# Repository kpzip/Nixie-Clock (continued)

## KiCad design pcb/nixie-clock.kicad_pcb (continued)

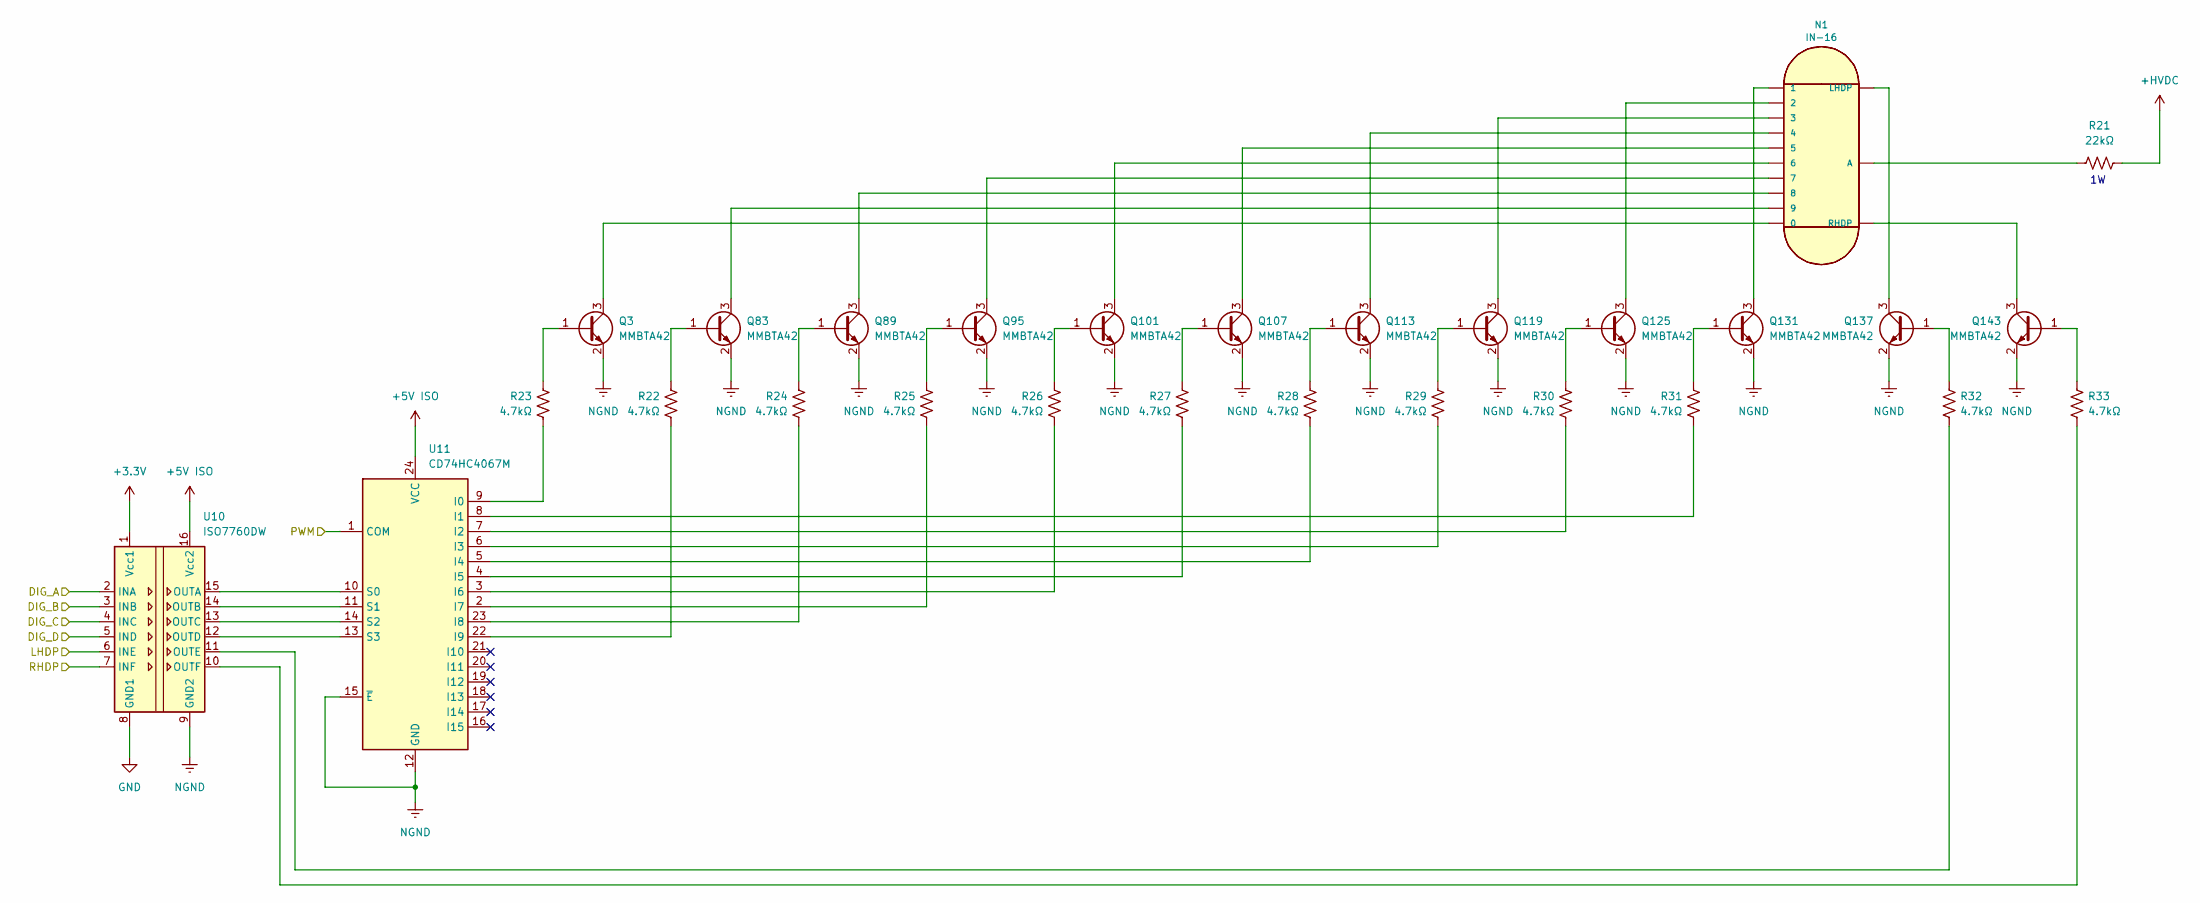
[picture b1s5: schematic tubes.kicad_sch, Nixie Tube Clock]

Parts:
N1: IN-16; nixies-us-IN-16
Q3, Q83, Q89, Q95, Q101, Q107, Q113, Q119, Q125, Q131, Q137, Q143: MMBTA42; SOT-23
R21: 22kΩ; R_2512_6332Metric
R22, R23, R24, R25, R26, R27, R28, R29, R30, R31, R32, R33: 4.7kΩ; R_0603_1608Metric
U10: ISO7760DW; SOIC-16W_7.5x10.3mm_P1.27mm
U11: CD74HC4067M; SOIC-24W_7.5x15.4mm_P1.27mm

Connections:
+3.3V: U10.1 (Vcc1); also elsewhere on the board
+5V ISO: U10.16 (Vcc2), U11.24 (VCC); also elsewhere on the board
+HVDC: R21.1; also elsewhere on the board
/Tube Shift Registers/Digit Tube & Driver 1/DIG_A: U10.2 (INA); also elsewhere on the board
/Tube Shift Registers/Digit Tube & Driver 1/DIG_B: U10.3 (INB); also elsewhere on the board
/Tube Shift Registers/Digit Tube & Driver 1/DIG_C: U10.4 (INC); also elsewhere on the board
/Tube Shift Registers/Digit Tube & Driver 1/DIG_D: U10.5 (IND); also elsewhere on the board
/Tube Shift Registers/Digit Tube & Driver 1/LHDP: U10.6 (INE); also elsewhere on the board
/Tube Shift Registers/Digit Tube & Driver 1/RHDP: U10.7 (INF); also elsewhere on the board
/Tube Shift Registers/PWM_1: U11.1 (COM); also elsewhere on the board
unnamed: N1.A, R21.2
unnamed: Q3.1 (B), R23.2
unnamed: N1.0, Q3.3 (C)
unnamed: Q83.1 (B), R22.2
unnamed: N1.9, Q83.3 (C)
unnamed: Q89.1 (B), R24.2
unnamed: N1.8, Q89.3 (C)
unnamed: Q95.1 (B), R25.2
unnamed: N1.7, Q95.3 (C)
unnamed: Q101.1 (B), R26.2
unnamed: N1.6, Q101.3 (C)
unnamed: Q107.1 (B), R27.2
unnamed: N1.5, Q107.3 (C)
unnamed: Q113.1 (B), R28.2
unnamed: N1.4, Q113.3 (C)
unnamed: Q119.1 (B), R29.2
unnamed: N1.3, Q119.3 (C)
unnamed: Q125.1 (B), R30.2
unnamed: N1.2, Q125.3 (C)
unnamed: Q131.1 (B), R31.2
unnamed: N1.1, Q131.3 (C)
unnamed: Q137.1 (B), R32.2
unnamed: N1.LHDP, Q137.3 (C)
unnamed: Q143.1 (B), R33.2
unnamed: N1.RHDP, Q143.3 (C)
unnamed: U10.15 (OUTA), U11.10 (S0)
unnamed: U10.14 (OUTB), U11.11 (S1)
unnamed: U10.13 (OUTC), U11.14 (S2)
unnamed: U10.12 (OUTD), U11.13 (S3)
unnamed: R32.1, U10.11 (OUTE)
unnamed: R33.1, U10.10 (OUTF)
unnamed: R23.1, U11.9 (I0)
unnamed: R31.1, U11.8 (I1)
unnamed: R30.1, U11.7 (I2)
unnamed: R29.1, U11.6 (I3)
unnamed: R28.1, U11.5 (I4)
unnamed: R27.1, U11.4 (I5)
unnamed: R26.1, U11.3 (I6)
unnamed: R25.1, U11.2 (I7)
unnamed: R24.1, U11.23 (I8)
unnamed: R22.1, U11.22 (I9)

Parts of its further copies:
N2, N3, N4, N5, N6: IN-16; nixies-us-IN-16
Q78, Q79, Q80, Q81, Q82, Q84, Q85, Q86, Q87, Q88, Q90, Q91, Q92, Q93, Q94, Q96, Q97, Q98, Q99, Q100, Q102, Q103, Q104, Q105, Q106, Q108, Q109, Q110, Q111, Q112, Q114, Q115, Q116, Q117, Q118, Q120, Q121, Q122, Q123, Q124, Q126, Q127, Q128, Q129, Q130, Q132, Q133, Q134, Q135, Q136, Q138, Q139, Q140, Q141, Q142, Q144, Q145, Q146, Q147, Q148: MMBTA42; SOT-23
R34, R35, R36, R37, R38, R39, R40, R41, R42, R43, R44, R45, R47, R48, R49, R50, R51, R52, R53, R54, R55, R56, R57, R58, R60, R61, R62, R63, R64, R65, R66, R67, R68, R69, R70, R71, R73, R74, R75, R76, R77, R78, R79, R80, R81, R82, R83, R84, R86, R87, R88, R89, R90, R91, R92, R93, R94, R95, R96, R97: 4.7kΩ; R_0603_1608Metric
R46, R59, R72, R85, R98: 22kΩ; R_2512_6332Metric
U12, U14, U16, U18, U20: ISO7760DW; SOIC-16W_7.5x10.3mm_P1.27mm
U13, U15, U17, U19, U21: CD74HC4067M; SOIC-24W_7.5x15.4mm_P1.27mm

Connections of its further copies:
+3.3V: U12.1 (Vcc1), U14.1 (Vcc1), U16.1 (Vcc1), U18.1 (Vcc1), U20.1 (Vcc1); also elsewhere on the board
+5V ISO: U12.16 (Vcc2), U13.24 (VCC), U14.16 (Vcc2), U15.24 (VCC), U16.16 (Vcc2), U17.24 (VCC), U18.16 (Vcc2), U19.24 (VCC), U20.16 (Vcc2), U21.24 (VCC); also elsewhere on the board
+HVDC: R46.1, R59.1, R72.1, R85.1, R98.1; also elsewhere on the board
/Tube Shift Registers/Digit Tube & Driver 2/DIG_A: U12.2 (INA); also elsewhere on the board
/Tube Shift Registers/Digit Tube & Driver 2/DIG_B: U12.3 (INB); also elsewhere on the board
/Tube Shift Registers/Digit Tube & Driver 2/DIG_C: U12.4 (INC); also elsewhere on the board
/Tube Shift Registers/Digit Tube & Driver 2/DIG_D: U12.5 (IND); also elsewhere on the board
/Tube Shift Registers/Digit Tube & Driver 2/LHDP: U12.6 (INE); also elsewhere on the board
/Tube Shift Registers/Digit Tube & Driver 2/RHDP: U12.7 (INF); also elsewhere on the board
/Tube Shift Registers/Digit Tube & Driver 3/DIG_A: U14.2 (INA); also elsewhere on the board
/Tube Shift Registers/Digit Tube & Driver 3/DIG_B: U14.3 (INB); also elsewhere on the board
/Tube Shift Registers/Digit Tube & Driver 3/DIG_C: U14.4 (INC); also elsewhere on the board
/Tube Shift Registers/Digit Tube & Driver 3/DIG_D: U14.5 (IND); also elsewhere on the board
/Tube Shift Registers/Digit Tube & Driver 3/LHDP: U14.6 (INE); also elsewhere on the board
/Tube Shift Registers/Digit Tube & Driver 3/RHDP: U14.7 (INF); also elsewhere on the board
/Tube Shift Registers/Digit Tube & Driver 4/DIG_A: U16.2 (INA); also elsewhere on the board
/Tube Shift Registers/Digit Tube & Driver 4/DIG_B: U16.3 (INB); also elsewhere on the board
/Tube Shift Registers/Digit Tube & Driver 4/DIG_C: U16.4 (INC); also elsewhere on the board
/Tube Shift Registers/Digit Tube & Driver 4/DIG_D: U16.5 (IND); also elsewhere on the board
/Tube Shift Registers/Digit Tube & Driver 4/LHDP: U16.6 (INE); also elsewhere on the board
/Tube Shift Registers/Digit Tube & Driver 4/RHDP: U16.7 (INF); also elsewhere on the board
/Tube Shift Registers/Digit Tube & Driver 5/DIG_A: U18.2 (INA); also elsewhere on the board
/Tube Shift Registers/Digit Tube & Driver 5/DIG_B: U18.3 (INB); also elsewhere on the board
/Tube Shift Registers/Digit Tube & Driver 5/DIG_C: U18.4 (INC); also elsewhere on the board
/Tube Shift Registers/Digit Tube & Driver 5/DIG_D: U18.5 (IND); also elsewhere on the board
/Tube Shift Registers/Digit Tube & Driver 5/LHDP: U18.6 (INE); also elsewhere on the board
/Tube Shift Registers/Digit Tube & Driver 5/RHDP: U18.7 (INF); also elsewhere on the board
/Tube Shift Registers/Digit Tube & Driver 6/DIG_A: U20.2 (INA); also elsewhere on the board
/Tube Shift Registers/Digit Tube & Driver 6/DIG_B: U20.3 (INB); also elsewhere on the board
/Tube Shift Registers/Digit Tube & Driver 6/DIG_C: U20.4 (INC); also elsewhere on the board
/Tube Shift Registers/Digit Tube & Driver 6/DIG_D: U20.5 (IND); also elsewhere on the board
/Tube Shift Registers/Digit Tube & Driver 6/LHDP: U20.6 (INE); also elsewhere on the board
/Tube Shift Registers/Digit Tube & Driver 6/RHDP: U20.7 (INF); also elsewhere on the board
/Tube Shift Registers/PWM_2: U13.1 (COM); also elsewhere on the board
/Tube Shift Registers/PWM_3: U15.1 (COM); also elsewhere on the board
/Tube Shift Registers/PWM_4: U17.1 (COM); also elsewhere on the board
/Tube Shift Registers/PWM_5: U19.1 (COM); also elsewhere on the board
/Tube Shift Registers/PWM_6: U21.1 (COM); also elsewhere on the board
unnamed: N2.A, R46.2
unnamed: N3.A, R59.2
unnamed: N4.A, R72.2
unnamed: N5.A, R85.2
unnamed: N6.A, R98.2
unnamed: Q78.1 (B), R34.2
unnamed: N2.0, Q78.3 (C)
unnamed: Q79.1 (B), R47.2
unnamed: N3.0, Q79.3 (C)
unnamed: Q80.1 (B), R60.2
unnamed: N4.0, Q80.3 (C)
unnamed: Q81.1 (B), R73.2
unnamed: N5.0, Q81.3 (C)
unnamed: Q82.1 (B), R86.2
unnamed: N6.0, Q82.3 (C)
unnamed: Q84.1 (B), R35.2
unnamed: N2.9, Q84.3 (C)
unnamed: Q85.1 (B), R48.2
unnamed: N3.9, Q85.3 (C)
unnamed: Q86.1 (B), R61.2
unnamed: N4.9, Q86.3 (C)
unnamed: Q87.1 (B), R74.2
unnamed: N5.9, Q87.3 (C)
unnamed: Q88.1 (B), R87.2
unnamed: N6.9, Q88.3 (C)
unnamed: Q90.1 (B), R36.2
unnamed: N2.8, Q90.3 (C)
unnamed: Q91.1 (B), R49.2
unnamed: N3.8, Q91.3 (C)
unnamed: Q92.1 (B), R62.2
unnamed: N4.8, Q92.3 (C)
unnamed: Q93.1 (B), R75.2
unnamed: N5.8, Q93.3 (C)
unnamed: Q94.1 (B), R88.2
unnamed: N6.8, Q94.3 (C)
unnamed: Q96.1 (B), R37.2
unnamed: N2.7, Q96.3 (C)
unnamed: Q97.1 (B), R50.2
unnamed: N3.7, Q97.3 (C)
unnamed: Q98.1 (B), R63.2
unnamed: N4.7, Q98.3 (C)
unnamed: Q99.1 (B), R76.2
unnamed: N5.7, Q99.3 (C)
unnamed: Q100.1 (B), R89.2
unnamed: N6.7, Q100.3 (C)
unnamed: Q102.1 (B), R38.2
unnamed: N2.6, Q102.3 (C)
unnamed: Q103.1 (B), R51.2
unnamed: N3.6, Q103.3 (C)
unnamed: Q104.1 (B), R64.2
unnamed: N4.6, Q104.3 (C)
unnamed: Q105.1 (B), R77.2
unnamed: N5.6, Q105.3 (C)
unnamed: Q106.1 (B), R90.2
unnamed: N6.6, Q106.3 (C)
unnamed: Q108.1 (B), R39.2
unnamed: N2.5, Q108.3 (C)
unnamed: Q109.1 (B), R52.2
unnamed: N3.5, Q109.3 (C)
unnamed: Q110.1 (B), R65.2
unnamed: N4.5, Q110.3 (C)
unnamed: Q111.1 (B), R78.2
unnamed: N5.5, Q111.3 (C)
unnamed: Q112.1 (B), R91.2
unnamed: N6.5, Q112.3 (C)
unnamed: Q114.1 (B), R40.2
unnamed: N2.4, Q114.3 (C)
unnamed: Q115.1 (B), R53.2
unnamed: N3.4, Q115.3 (C)
unnamed: Q116.1 (B), R66.2
unnamed: N4.4, Q116.3 (C)
unnamed: Q117.1 (B), R79.2
unnamed: N5.4, Q117.3 (C)
unnamed: Q118.1 (B), R92.2
unnamed: N6.4, Q118.3 (C)
unnamed: Q120.1 (B), R41.2
unnamed: N2.3, Q120.3 (C)
unnamed: Q121.1 (B), R54.2
unnamed: N3.3, Q121.3 (C)
unnamed: Q122.1 (B), R67.2
unnamed: N4.3, Q122.3 (C)
unnamed: Q123.1 (B), R80.2
unnamed: N5.3, Q123.3 (C)
unnamed: Q124.1 (B), R93.2
unnamed: N6.3, Q124.3 (C)
unnamed: Q126.1 (B), R42.2
unnamed: N2.2, Q126.3 (C)
unnamed: Q127.1 (B), R55.2
unnamed: N3.2, Q127.3 (C)
unnamed: Q128.1 (B), R68.2
unnamed: N4.2, Q128.3 (C)
unnamed: Q129.1 (B), R81.2
unnamed: N5.2, Q129.3 (C)
unnamed: Q130.1 (B), R94.2
unnamed: N6.2, Q130.3 (C)
unnamed: Q132.1 (B), R43.2
unnamed: N2.1, Q132.3 (C)
unnamed: Q133.1 (B), R56.2
unnamed: N3.1, Q133.3 (C)
unnamed: Q134.1 (B), R69.2
unnamed: N4.1, Q134.3 (C)
unnamed: Q135.1 (B), R82.2
unnamed: N5.1, Q135.3 (C)
unnamed: Q136.1 (B), R95.2
unnamed: N6.1, Q136.3 (C)
unnamed: Q138.1 (B), R44.2
unnamed: N2.LHDP, Q138.3 (C)
unnamed: Q139.1 (B), R57.2
unnamed: N3.LHDP, Q139.3 (C)
unnamed: Q140.1 (B), R70.2
unnamed: N4.LHDP, Q140.3 (C)
unnamed: Q141.1 (B), R83.2
unnamed: N5.LHDP, Q141.3 (C)
unnamed: Q142.1 (B), R96.2
unnamed: N6.LHDP, Q142.3 (C)
unnamed: Q144.1 (B), R45.2
unnamed: N2.RHDP, Q144.3 (C)
unnamed: Q145.1 (B), R58.2
unnamed: N3.RHDP, Q145.3 (C)
unnamed: Q146.1 (B), R71.2
unnamed: N4.RHDP, Q146.3 (C)
unnamed: Q147.1 (B), R84.2
unnamed: N5.RHDP, Q147.3 (C)
unnamed: Q148.1 (B), R97.2
unnamed: N6.RHDP, Q148.3 (C)
unnamed: U12.15 (OUTA), U13.10 (S0)
unnamed: U12.14 (OUTB), U13.11 (S1)
unnamed: U12.13 (OUTC), U13.14 (S2)
unnamed: U12.12 (OUTD), U13.13 (S3)
unnamed: R44.1, U12.11 (OUTE)
unnamed: R45.1, U12.10 (OUTF)
unnamed: R34.1, U13.9 (I0)
unnamed: R43.1, U13.8 (I1)
unnamed: R42.1, U13.7 (I2)
unnamed: R41.1, U13.6 (I3)
unnamed: R40.1, U13.5 (I4)
unnamed: R39.1, U13.4 (I5)
unnamed: R38.1, U13.3 (I6)
unnamed: R37.1, U13.2 (I7)
unnamed: R36.1, U13.23 (I8)
unnamed: R35.1, U13.22 (I9)
unnamed: U14.15 (OUTA), U15.10 (S0)
unnamed: U14.14 (OUTB), U15.11 (S1)
unnamed: U14.13 (OUTC), U15.14 (S2)
unnamed: U14.12 (OUTD), U15.13 (S3)
unnamed: R57.1, U14.11 (OUTE)
unnamed: R58.1, U14.10 (OUTF)
unnamed: R47.1, U15.9 (I0)
unnamed: R56.1, U15.8 (I1)
unnamed: R55.1, U15.7 (I2)
unnamed: R54.1, U15.6 (I3)
unnamed: R53.1, U15.5 (I4)
unnamed: R52.1, U15.4 (I5)
unnamed: R51.1, U15.3 (I6)
unnamed: R50.1, U15.2 (I7)
unnamed: R49.1, U15.23 (I8)
unnamed: R48.1, U15.22 (I9)
unnamed: U16.15 (OUTA), U17.10 (S0)
unnamed: U16.14 (OUTB), U17.11 (S1)
unnamed: U16.13 (OUTC), U17.14 (S2)
unnamed: U16.12 (OUTD), U17.13 (S3)
unnamed: R70.1, U16.11 (OUTE)
unnamed: R71.1, U16.10 (OUTF)
unnamed: R60.1, U17.9 (I0)
unnamed: R69.1, U17.8 (I1)
unnamed: R68.1, U17.7 (I2)
unnamed: R67.1, U17.6 (I3)
unnamed: R66.1, U17.5 (I4)
unnamed: R65.1, U17.4 (I5)
unnamed: R64.1, U17.3 (I6)
unnamed: R63.1, U17.2 (I7)
unnamed: R62.1, U17.23 (I8)
unnamed: R61.1, U17.22 (I9)
unnamed: U18.15 (OUTA), U19.10 (S0)
unnamed: U18.14 (OUTB), U19.11 (S1)
unnamed: U18.13 (OUTC), U19.14 (S2)
unnamed: U18.12 (OUTD), U19.13 (S3)
unnamed: R83.1, U18.11 (OUTE)
unnamed: R84.1, U18.10 (OUTF)
unnamed: R73.1, U19.9 (I0)
unnamed: R82.1, U19.8 (I1)
unnamed: R81.1, U19.7 (I2)
unnamed: R80.1, U19.6 (I3)
unnamed: R79.1, U19.5 (I4)
unnamed: R78.1, U19.4 (I5)
unnamed: R77.1, U19.3 (I6)
unnamed: R76.1, U19.2 (I7)
unnamed: R75.1, U19.23 (I8)
unnamed: R74.1, U19.22 (I9)
unnamed: U20.15 (OUTA), U21.10 (S0)
unnamed: U20.14 (OUTB), U21.11 (S1)
unnamed: U20.13 (OUTC), U21.14 (S2)
unnamed: U20.12 (OUTD), U21.13 (S3)
unnamed: R96.1, U20.11 (OUTE)
unnamed: R97.1, U20.10 (OUTF)
unnamed: R86.1, U21.9 (I0)
unnamed: R95.1, U21.8 (I1)
unnamed: R94.1, U21.7 (I2)
unnamed: R93.1, U21.6 (I3)
unnamed: R92.1, U21.5 (I4)
unnamed: R91.1, U21.4 (I5)
unnamed: R90.1, U21.3 (I6)
unnamed: R89.1, U21.2 (I7)
unnamed: R88.1, U21.23 (I8)
unnamed: R87.1, U21.22 (I9)

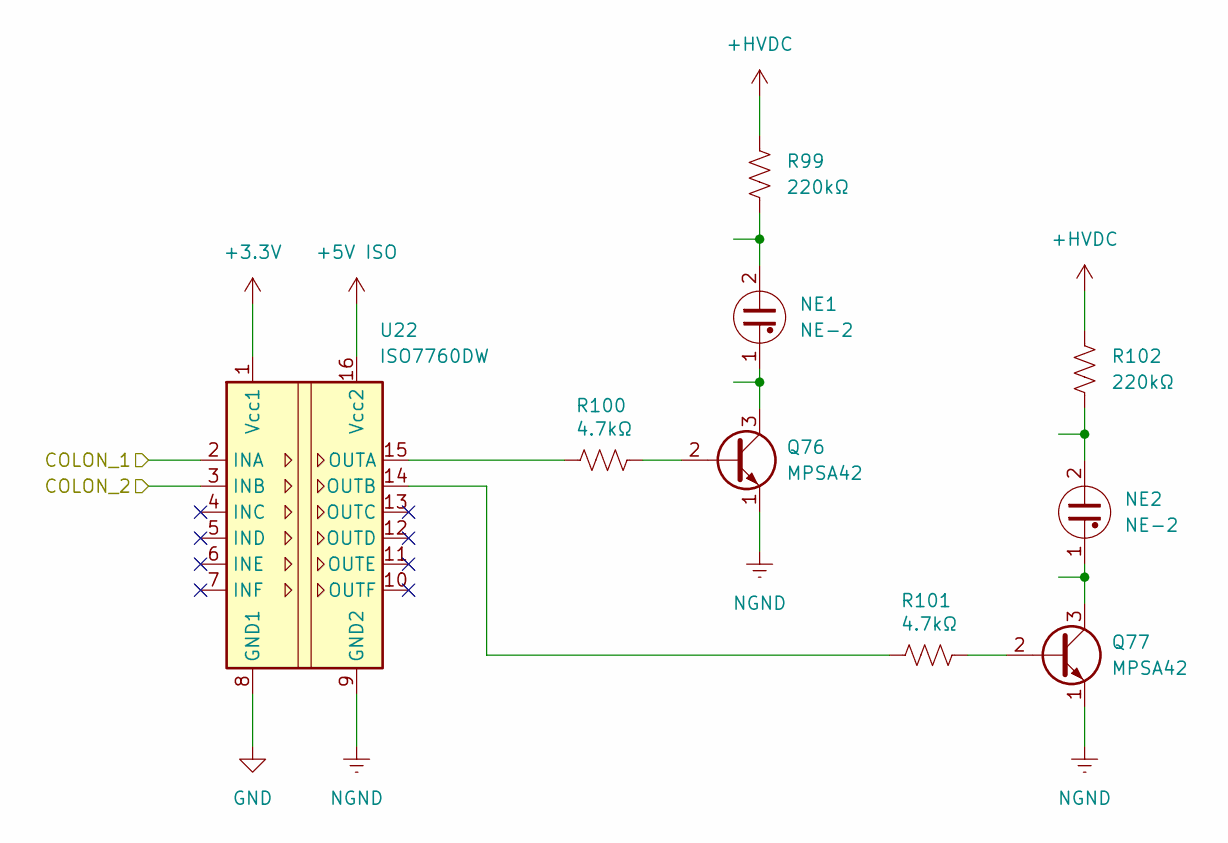
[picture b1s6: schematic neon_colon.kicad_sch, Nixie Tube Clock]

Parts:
NE1, NE2: NE-2; mynixies-NE2-NEON-BULB-DRILL
Q76, Q77: MPSA42; TO-92_Inline
R99, R102: 220kΩ; R_0603_1608Metric
R100, R101: 4.7kΩ; R_0603_1608Metric
U22: ISO7760DW; SOIC-16W_7.5x10.3mm_P1.27mm

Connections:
+3.3V: U22.1 (Vcc1); also elsewhere on the board
+5V ISO: U22.16 (Vcc2); also elsewhere on the board
+HVDC: R99.1, R102.1; also elsewhere on the board
/Tube Shift Registers/Colons/COLON_1: U22.2 (INA); also elsewhere on the board
/Tube Shift Registers/Colons/COLON_2: U22.3 (INB); also elsewhere on the board
unnamed: NE1.2, R99.2
unnamed: NE2.2, R102.2
unnamed: Q76.2 (B), R100.1
unnamed: NE1.1, Q76.3 (C)
unnamed: Q77.2 (B), R101.1
unnamed: NE2.1, Q77.3 (C)
unnamed: R100.2, U22.15 (OUTA)
unnamed: R101.2, U22.14 (OUTB)

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
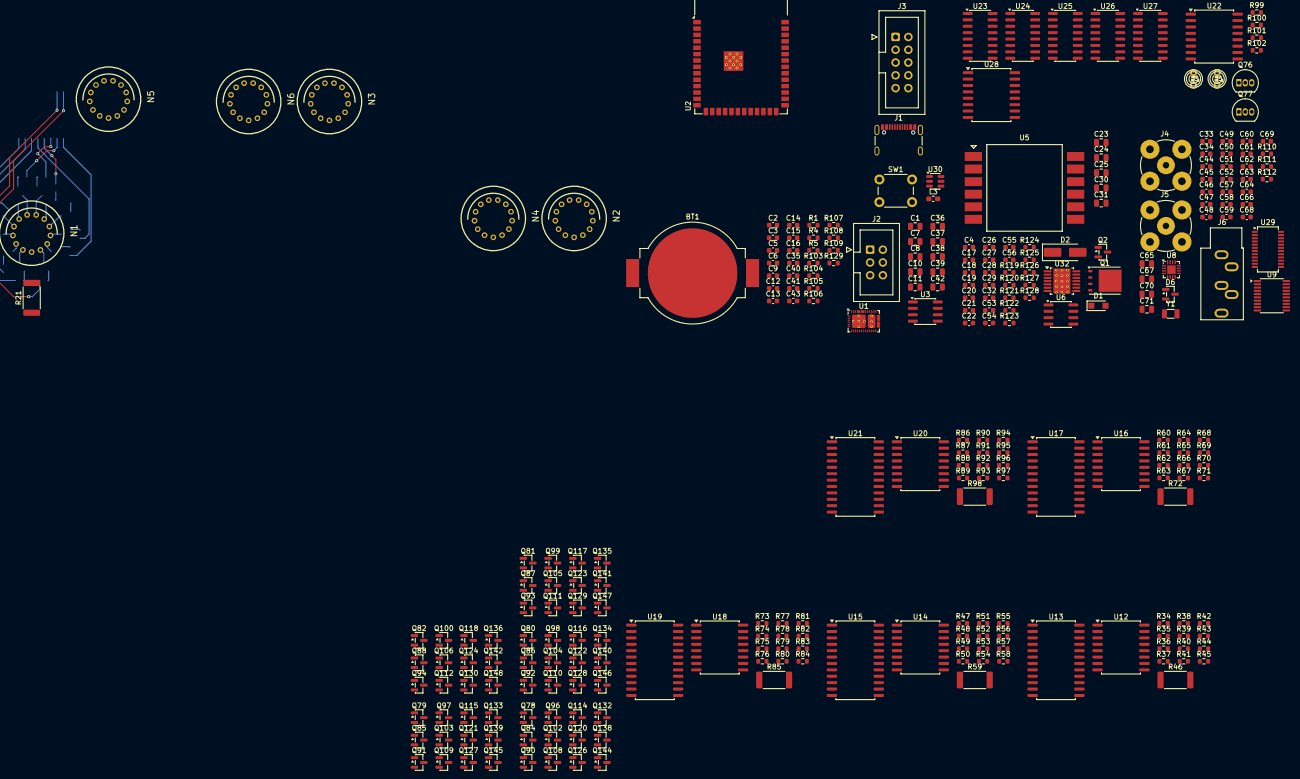
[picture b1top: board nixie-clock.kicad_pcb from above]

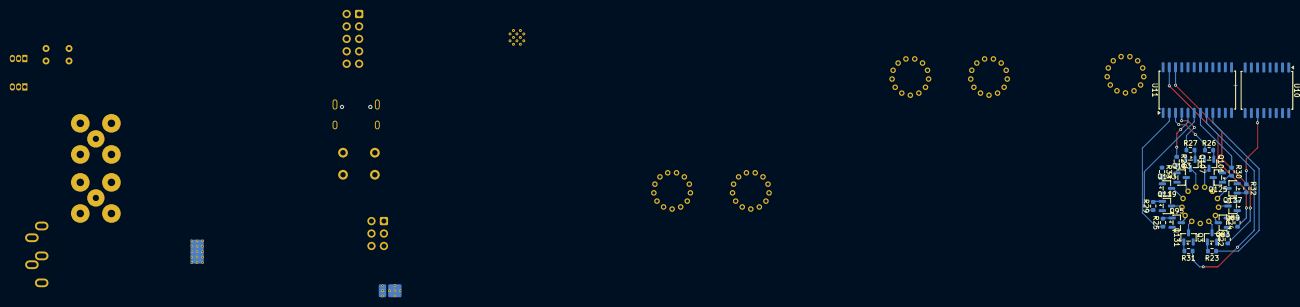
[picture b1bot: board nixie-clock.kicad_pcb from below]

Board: 4 copper layers, 303 parts (26 on the bottom side), 391 nets.

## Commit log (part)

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2026-04-24 work = force * distance
